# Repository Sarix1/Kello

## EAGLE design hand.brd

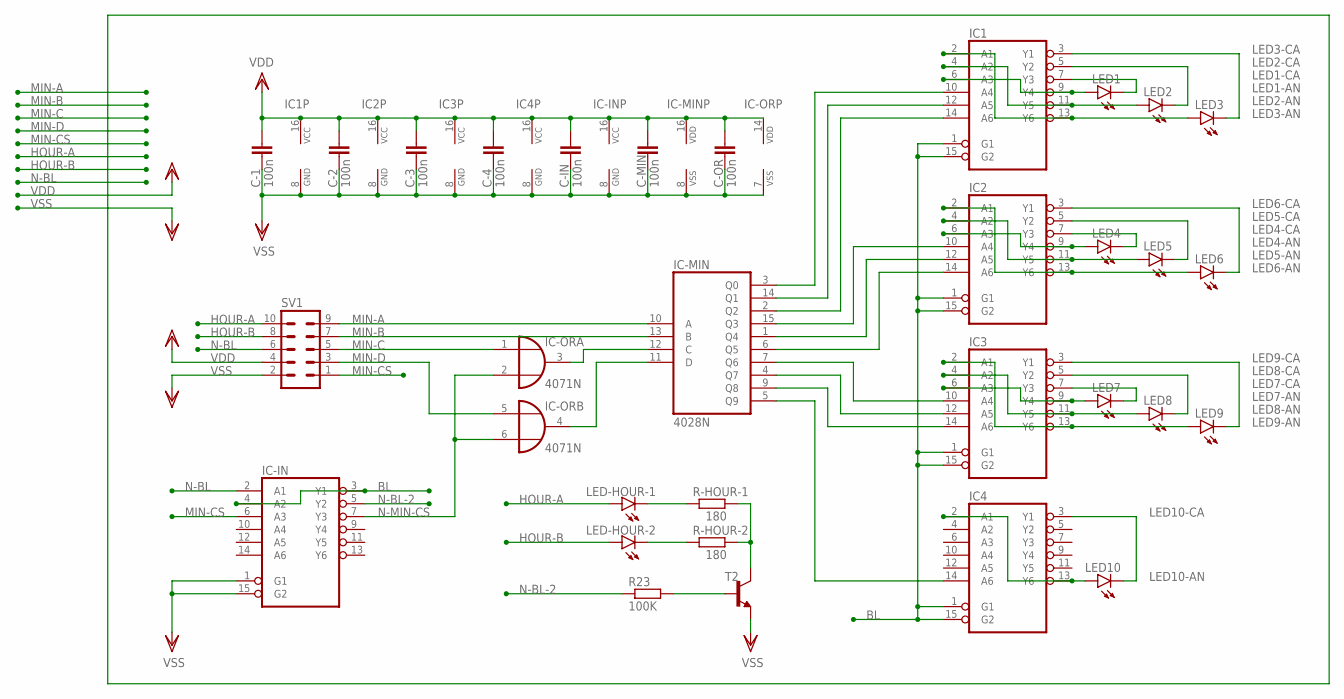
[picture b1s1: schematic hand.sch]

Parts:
C-1, C-2, C-3, C-4: 100n; C050-025X075
C-IN: 100n; C050-025X075
C-MIN: 100n; C050-025X075
C-OR: 100n; C050-025X075
IC1, IC2, IC3, IC4: 74HC366N; DIL16
IC-IN: 74HC366N; DIL16
IC-MIN: 4028N; DIL16
IC-OR: 4071N; DIL14
LED1, LED2, LED3, LED4, LED5, LED6, LED7, LED8, LED9, LED10: LED5MM
LED-HOUR-1, LED-HOUR-2: LED10MM
R23: 100K; 0207/10
R-HOUR-1, R-HOUR-2: 180; 0207/10
SV1: ML10
T2: BC547-NPN-TO92-CBE; TO92-CBE

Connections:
BL: IC1.1 (G1), IC1.15 (G2), IC2.1 (G1), IC2.15 (G2), IC3.1 (G1), IC3.15 (G2), IC4.1 (G1), IC4.15 (G2), IC-IN.3 (Y1), IC-IN.4 (A2)
HOUR-A: LED-HOUR-1.A, SV1.10
HOUR-B: LED-HOUR-2.A, SV1.8
LED1-AN: IC1.6 (A3), IC1.9 (Y4), LED1.A
LED1-CA: IC1.7 (Y3), LED1.K (C)
LED2-AN: IC1.4 (A2), IC1.11 (Y5), LED2.A
LED2-CA: IC1.5 (Y2), LED2.K (C)
LED3-AN: IC1.2 (A1), IC1.13 (Y6), LED3.A
LED3-CA: IC1.3 (Y1), LED3.K (C)
LED4-AN: IC2.6 (A3), IC2.9 (Y4), LED4.A
LED4-CA: IC2.7 (Y3), LED4.K (C)
LED5-AN: IC2.4 (A2), IC2.11 (Y5), LED5.A
LED5-CA: IC2.5 (Y2), LED5.K (C)
LED6-AN: IC2.2 (A1), IC2.13 (Y6), LED6.A
LED6-CA: IC2.3 (Y1), LED6.K (C)
LED7-AN: IC3.6 (A3), IC3.9 (Y4), LED7.A
LED7-CA: IC3.7 (Y3), LED7.K (C)
LED8-AN: IC3.4 (A2), IC3.11 (Y5), LED8.A
LED8-CA: IC3.5 (Y2), LED8.K (C)
LED9-AN: IC3.2 (A1), IC3.13 (Y6), LED9.A
LED9-CA: IC3.3 (Y1), LED9.K (C)
LED10-AN: IC4.2 (A1), IC4.13 (Y6), LED10.A
LED10-CA: IC4.3 (Y1), LED10.K (C)
MIN-A: IC-MIN.10 (A), SV1.9
MIN-B: IC-MIN.13 (B), SV1.7
MIN-C: IC-OR.1 (I0), SV1.5
MIN-CS: IC-IN.6 (A3), SV1.1
MIN-D: IC-OR.5 (I0), SV1.3
unnamed: IC3.10 (A4), IC-MIN.7 (Q6)
unnamed: IC1.10 (A4), IC-MIN.3 (Q0)
unnamed: IC2.14 (A6), IC-MIN.6 (Q5)
unnamed: IC1.12 (A5), IC-MIN.14 (Q1)
unnamed: IC1.14 (A6), IC-MIN.2 (Q2)
unnamed: IC2.10 (A4), IC-MIN.15 (Q3)
unnamed: IC2.12 (A5), IC-MIN.1 (Q4)
unnamed: IC3.12 (A5), IC-MIN.4 (Q7)
unnamed: IC3.14 (A6), IC-MIN.9 (Q8)
unnamed: IC4.14 (A6), IC-MIN.5 (Q9)
unnamed: IC-MIN.12 (C), IC-OR.3 (O)
unnamed: IC-MIN.11 (D), IC-OR.4 (O)
unnamed: R-HOUR-1.2, R-HOUR-2.2, T2.C
unnamed: LED-HOUR-1.K (C), R-HOUR-1.1
unnamed: LED-HOUR-2.K (C), R-HOUR-2.1
unnamed: R23.2, T2.B
N-BL: IC-IN.2 (A1), SV1.6
N-BL-2: IC-IN.5 (Y2), R23.1
N-MIN-CS: IC-IN.7 (Y3), IC-OR.2 (I1), IC-OR.6 (I1)
VDD: C-1.1, C-2.1, C-3.1, C-4.1, C-IN.1, C-MIN.1, C-OR.1, IC1.16 (VCC), IC2.16 (VCC), IC3.16 (VCC), IC4.16 (VCC), IC-IN.16 (VCC), IC-MIN.16 (VDD), IC-OR.14 (VDD), SV1.4
VSS: C-1.2, C-2.2, C-3.2, C-4.2, C-IN.2, C-MIN.2, C-OR.2, IC1.8 (GND), IC2.8 (GND), IC3.8 (GND), IC4.8 (GND), IC-IN.1 (G1), IC-IN.8 (GND), IC-IN.15 (G2), IC-MIN.8 (VSS), IC-OR.7 (VSS), SV1.2, T2.E

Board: 2 copper layers, 31 parts (19 on the bottom side), 49 nets, no tracks yet.

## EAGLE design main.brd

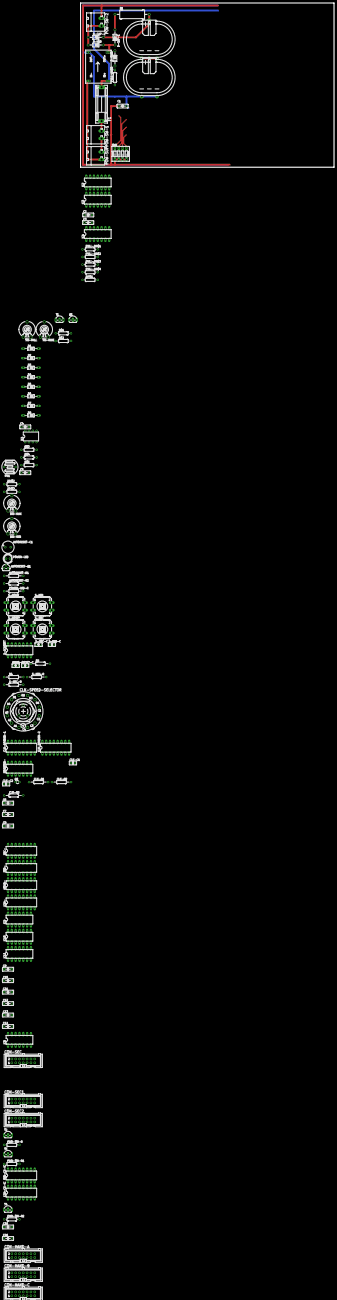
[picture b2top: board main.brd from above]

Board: 2 copper layers, 168.6 x 109.2 mm, 112 parts (0 on the bottom side), 119 nets.

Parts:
12H-: 4520N; DIL16
12H-CS-IC: 4028N; DIL16
AUTORESET-C1: 10uF; E3,5-8
AUTORESET-Q1: BC547; TO92
AUTORESET-R1: 100K; 0207/12
AUTORESET-R2: 10K; 0207/12
BRI-MAX: LI10
BRI-MIN: LI10
C1, C2, C3, C4, C5, C6, C7, C8, C9, C10, C11, C12, C13, C14, C15, C16: 100n; C050-025X075
CLK-C1, CLK-C2: 10pf; C025-025X050
CLK-DIVIDER-1, CLK-DIVIDER-2: 4520N; DIL16
CLK-R1, CLK-R2: 10M; 0207/12
CLK-R3: 330K; 0207/12
CLK-SPEED-SELECTOR: CK103X04
CON-HAND-A: ML14
CON-HAND-B: ML14
CON-HAND-C: ML14
CON-SEC, CON-SEC1, CON-SEC2: ML14
D1, D2, D3, D4, D5, D6, D7, D8: 1N4148DO35-10; DO35-10
D-CAP-1, D-CAP-2: 1N4004; DO41-10
D-MAIN: 1N4004; DO41-10
D-VDD: 1N4004; DO41-10
DIV$1, DIV$2, DIV$3: 1K; 0207/10
F1: SH22,5
HOUR-: 4518N; DIL16
HOUR-C: 100n; C025-025X050
IC1: TL072P; DIL08
IC2, IC4, IC10: 4071N; DIL14
IC3, IC9: 4081N; DIL14
IC5: 4001N; DIL14
IC11: 4030N; DIL14
INVERTER-: 4069N; DIL14
MIN-: 4518N; DIL16
MIN-CS-IC: 4028N; DIL16
PH1: VT43N1; VT400
POW-SUP: MSTBA2
POW-SW-1, POW-SW-2: MSTBA2
POWER-LED: LED5MM
POWER-LED-R: 270; 0207/12
PULL-DN$0, PULL-DN$1, PULL-DN$2, PULL-DN$3, PULL-DN$4: 0207/10
PWR-TRI-R, PWR-TRI-R1, PWR-TRI-R2: 1K; 0207/10
Q1: BC557; TO92-EBC
Q8: 32768Hz; TC26V
R1: 0617/22
R2, R4: 570K; 0207/12
R$1, R$2: 180; 0207/10
R$3, R$4, R$5: 4K; 0207/10
RESET-C: 100n; C025-025X050
S-HOUR: RACON12
S-MIN: RACON12
S-MIN-C: 100n; C025-025X050
S-MIN-R: 570K; 0207/12
S-RESET: RACON12
S-SCHMITT: 40106N; DIL14
S-SEC: RACON12
S-SEC-C: 100n; C025-025X050
S-SEC-R: 570K; 0207/12
SEC-: 4518N; DIL16
SUPER-C1, SUPER-C2: HVC90F
SW1: EDG-04
T1, T2, T3, T4: TO92-CBE
TRI-FALL: LI10
TRI-RISE: LI10
U$1: MP1584; DC-BRICK

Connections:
0V-EXT: POW-SUP.2, U$1.IN1-, U$1.IN2-
1HZ: CLK-DIVIDER-2.13, CLK-SPEED-SELECTOR.A2, IC2.8
2HZ: CLK-DIVIDER-2.12, CLK-SPEED-SELECTOR.A3
4HZ: CLK-DIVIDER-2.11, CLK-SPEED-SELECTOR.A4
8HZ: CLK-DIVIDER-2.6, CLK-DIVIDER-2.10, CLK-SPEED-SELECTOR.B1
9V: CON-SEC.14, CON-SEC1.14, CON-SEC2.14, F1.2, U$1.IN1+, U$1.IN2+
9V-EXT: POW-SUP.1, POW-SW-1.2
9V-IN: F1.1, POW-SW-1.1
12H-A: 12H-.3, 12H-CS-IC.10
12H-B: 12H-.4, 12H-CS-IC.13
12H-C: 12H-.5, IC9.12
12H-D: 12H-.6, IC9.13
16HZ: CLK-DIVIDER-2.5, CLK-SPEED-SELECTOR.B2
32HZ: CLK-DIVIDER-2.4, CLK-SPEED-SELECTOR.B3
64HZ: CLK-DIVIDER-2.3, CLK-SPEED-SELECTOR.B4
128HZ: CLK-DIVIDER-1.14, CLK-DIVIDER-2.2, CLK-SPEED-SELECTOR.C1
256HZ: CLK-DIVIDER-1.13, CLK-SPEED-SELECTOR.C2
512HZ: CLK-DIVIDER-1.12, CLK-SPEED-SELECTOR.C3
1024HZ: CLK-DIVIDER-1.11, CLK-SPEED-SELECTOR.C4
2048HZ: CLK-DIVIDER-1.6, CLK-DIVIDER-1.10
ALW: IC2.2, IC4.3
AUTO-R: AUTORESET-Q1.3, AUTORESET-R2.2, IC2.13
BLI: IC2.9, IC4.10
BRI: IC2.6, IC4.4
BRI-REF: BRI-MIN.E, IC1.6, PH1.2
BTN-HOUR: IC11.9, S-SCHMITT.6
BTN-MIN: IC11.6, S-SCHMITT.4
BTN-RESET: IC2.12, S-SCHMITT.8
BTN-SEC: IC11.2, S-SCHMITT.2
CLK: CLK-SPEED-SELECTOR.A, CLK-SPEED-SELECTOR.B, CLK-SPEED-SELECTOR.C, IC11.1
CLK-C2-R3: CLK-C2.1, CLK-R3.2, Q8.2
GND-7SEG: CON-SEC.10, CON-SEC.13, CON-SEC1.10, CON-SEC1.13, CON-SEC2.10, CON-SEC2.13, T3.C
GND-HAND: 12H-CS-IC.8, 12H-CS-IC.11, 12H-CS-IC.12, C15.2, C16.2, MIN-CS-IC.8, MIN-CS-IC.11, T4.C
GND-TRI: C4.2, C5.2, D4.C, DIV$3.1, IC1.4, R$2.1, R$4.1, T2.C
HOUR-ONE-A: CON-SEC2.8, HOUR-.3
HOUR-ONE-B: CON-SEC2.6, HOUR-.4
HOUR-ONE-C: CON-SEC2.4, HOUR-.5, IC9.8
HOUR-ONE-D: CON-SEC2.2, HOUR-.6, HOUR-.10
HOUR-TEN-A: CON-SEC2.7, HOUR-.11, IC5.1
HOUR-TEN-B: CON-SEC2.5, HOUR-.12, IC5.2, IC9.9
HOUR-TEN-CD: CON-SEC2.1, CON-SEC2.3, IC3.10
MAIN: D-MAIN.C, IC2.1, PULL-DN$0.2
MIN-ONE-A: CON-SEC1.8, MIN-.3
MIN-ONE-B: CON-SEC1.6, MIN-.4
MIN-ONE-C: CON-SEC1.4, MIN-.5
MIN-ONE-D: CON-SEC1.2, MIN-.6, MIN-.10
MIN-TEN-A: CON-SEC1.7, MIN-.11, MIN-CS-IC.10
MIN-TEN-B: CON-SEC1.5, IC9.5, MIN-.12, MIN-CS-IC.13
MIN-TEN-C: CON-SEC1.3, IC9.6, MIN-.13, MIN-CS-IC.12
MIN-TEN-D: CON-SEC1.1, MIN-.14
unnamed: IC4.12, IC4.13, PULL-DN$3.2, SW1.8
unnamed: IC4.8, IC4.9, PULL-DN$2.2, SW1.7
unnamed: IC4.5, IC4.6, PULL-DN$1.2, SW1.6
unnamed: D-CAP-1.A, D-MAIN.A, D-VDD.A, U$1.OUT1+, U$1.OUT2+
unnamed: D-CAP-1.C, R1.1
unnamed: D-CAP-2.A, R1.2, SUPER-C1.PLUS$1
unnamed: SUPER-C1.MINUS$1, SUPER-C1.MINUS$2, SUPER-C2.PLUS$1
unnamed: IC4.1, IC4.2, PULL-DN$4.2, SW1.5
unnamed: IC2.4, IC3.2
unnamed: IC2.10, IC3.6
unnamed: D1.C, D2.A
unnamed: IC1.3, R$3.1, R$4.2, R$5.2
unnamed: D2.C, DIV$1.2, Q1.B
unnamed: D3.A, DIV$1.1, T1.B
unnamed: R$1.1, TRI-RISE.E
unnamed: T1.E, TRI-FALL.E
unnamed: Q1.E, TRI-RISE.S
unnamed: R$2.2, TRI-FALL.S
unnamed: D6.C, D8.C, T1.C
unnamed: D5.A, D7.A, Q1.C
unnamed: D3.C, D4.A
unnamed: BRI-MAX.E, DIV$2.1
unnamed: BRI-MAX.S, PH1.1
unnamed: BRI-MIN.S, DIV$3.2
unnamed: D5.C, D8.A, IC1.1, R$5.1
unnamed: S-SCHMITT.1, S-SEC.1, S-SEC-C.2, S-SEC-R.1
unnamed: S-MIN.1, S-MIN-C.2, S-MIN-R.1, S-SCHMITT.3
unnamed: HOUR-C.2, R4.1, S-HOUR.1, S-SCHMITT.5
unnamed: RESET-C.1, S-RESET.3
unnamed: S-MIN.3, S-MIN-C.1
unnamed: R2.1, RESET-C.2, S-RESET.1, S-SCHMITT.9
unnamed: PWR-TRI-R.1, T2.B
unnamed: PWR-TRI-R1.1, T3.B
unnamed: PWR-TRI-R2.1, T4.B
unnamed: CLK-DIVIDER-1.2, INVERTER-.4
unnamed: 12H-.7, IC10.11
unnamed: IC9.10, IC10.8
unnamed: IC9.3, IC10.1, IC11.5
unnamed: IC10.2, IC10.4, MIN-.7, MIN-.15
unnamed: IC9.4, IC10.5, IC11.8
unnamed: IC9.11, IC10.13
unnamed: HOUR-.7, HOUR-.15, IC10.6, IC10.10
unnamed: IC11.3, SEC-.2
unnamed: IC10.3, SEC-.7, SEC-.15
unnamed: CLK-R1.1, CLK-R2.2
unnamed: IC11.4, MIN-.2
unnamed: 12H-.2, HOUR-.2, IC11.10
unnamed: AUTORESET-C1.+, AUTORESET-Q1.2, AUTORESET-R1.2
unnamed: IC3.9, IC5.3
unnamed: POWER-LED.A, POWER-LED-R.2
N-BL: CON-SEC.11, CON-SEC1.11, CON-SEC2.11, IC3.3, IC3.5
PWM: IC1.7, IC2.5
PWR: IC2.3, IC3.1, PWR-TRI-R.2, PWR-TRI-R1.2, PWR-TRI-R2.2
RESET: IC2.11, IC10.9, IC10.12
SEC-ONE-A: CON-SEC.8, SEC-.3
SEC-ONE-B: CON-SEC.6, SEC-.4
SEC-ONE-C: CON-SEC.4, SEC-.5
SEC-ONE-D: CON-SEC.2, SEC-.6, SEC-.10
SEC-TEN-A: CON-SEC.7, SEC-.11
SEC-TEN-B: CON-SEC.5, IC9.1, SEC-.12
SEC-TEN-C: CON-SEC.3, IC9.2, SEC-.13
SEC-TEN-D: CON-SEC.1, SEC-.14
SIGNAL-CLK-XTAL-1: CLK-C1.1, CLK-R1.2, INVERTER-.1, Q8.1
SIGNAL-CLK-XTAL-2: CLK-R2.1, CLK-R3.1, INVERTER-.2, INVERTER-.3
TRI-WAVE: C4.1, D6.A, D7.C, IC1.2, IC1.5
VDD: 12H-.16, 12H-CS-IC.16, AUTORESET-R1.1, AUTORESET-R2.1, C1.1, C2.1, C3.1, C5.1, C6.1, C7.1, C8.1, C9.1, C10.1, C11.1, C12.1, C13.1, C14.1, C15.1, C16.1, CLK-DIVIDER-1.16, CLK-DIVIDER-2.16, CON-SEC.9, CON-SEC.12, CON-SEC1.9, CON-SEC1.12, CON-SEC2.9, CON-SEC2.12, D1.A, DIV$2.2, HOUR-.16, HOUR-C.1, IC1.8, IC2.14, IC3.14, IC4.14, IC5.14, IC9.14, IC10.14, IC11.14, INVERTER-.14, MIN-.16, MIN-CS-IC.16, POW-SW-2.1, POWER-LED-R.1, R$1.2, R$3.2, S-HOUR.3, S-SCHMITT.14, S-SEC.3, S-SEC-C.1, SEC-.16, SW1.1, SW1.2, SW1.3, SW1.4
VDD-IN: D-CAP-2.C, D-VDD.C, POW-SW-2.2
VSS: 12H-.8, AUTORESET-C1.-, AUTORESET-Q1.1, C1.2, C2.2, C3.2, C6.2, C7.2, C8.2, C9.2, C10.2, C11.2, C12.2, C13.2, C14.2, CLK-C1.2, CLK-C2.2, CLK-DIVIDER-1.1, CLK-DIVIDER-1.7, CLK-DIVIDER-1.8, CLK-DIVIDER-1.9, CLK-DIVIDER-1.15, CLK-DIVIDER-2.1, CLK-DIVIDER-2.7, CLK-DIVIDER-2.8, CLK-DIVIDER-2.9, CLK-DIVIDER-2.15, CLK-SPEED-SELECTOR.A1, HOUR-.1, HOUR-.8, HOUR-.9, IC2.7, IC3.7, IC4.7, IC5.7, IC9.7, IC10.7, IC11.7, INVERTER-.7, MIN-.1, MIN-.8, MIN-.9, POWER-LED.K, PULL-DN$0.1, PULL-DN$1.1, PULL-DN$2.1, PULL-DN$3.1, PULL-DN$4.1, R2.2, R4.2, S-MIN-R.2, S-SCHMITT.7, S-SEC-R.2, SEC-.1, SEC-.8, SEC-.9, SUPER-C2.MINUS$1, SUPER-C2.MINUS$2, T2.E, T3.E, T4.E, U$1.OUT1-, U$1.OUT2-
ZER: IC3.8, IC4.11
